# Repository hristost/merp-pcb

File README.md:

This is a PCB for a bluetooth split 12x5 ortholinear keyboard:
* Based on Adafruit's 32u4 
[Feather](https://github.com/adafruit/Adafruit-Feather-32u4-Bluefruit-LE-PCB)
beard. 
* Wireless (BLE) and wired (USB-C) mode.
* LED backlight.
* There are two 6x2 halves with identical PCBs. The _master_ half runs the QMK
firmware, and handles USB, BLE and battery charging. The _slave_ half is
responsible for only reporting its state to _master_ over I2C.
* Extra TRRS jack on the _slave_ half, making it possible to chain other I2C 
peripherals (think pedals).
* The board is flashed with the QMK firmware -- see my
[fork](https://github.com/hristost/qmk_firmware/tree/hristost_merp/keyboards/merp)
.

## Bluetooth
The PCB uses the Raytac MDBT-40 module for bluetooth. QMK has built-in support
for that module when flashed with Adafruit's 
[SPIFriend](https://github.com/adafruit/Adafruit_BluefruitLE_Firmware) firmware.

Since the Bluetooth module connects to the SPI bus, remember to flash the CPU
_before_ the Bluetooth module. Otherwise, the SPI bus will be taken and ICSP 
won't work.

## LED backlight
This keyboard has LED backlight, however:
* The drivers I used (TLC59711) draw quite some current on stand-by that makes
them unsuitable for battery-powered devices. I chose them because I already had
some left over from a previous project.
* Since the keyboard is "borderless", some switches have been rotated so that
components can fit between them. As a result, the backlight is uneven and would
not be suitable for actual backlit keys.
* The two halves operate backlight independently as of now, so any advanced
animation would have to utilise the I2C bus.
    
## Known issues:
I designed this keyboard just for fun and as such it has some shortcomings:
* The BLE module is somewhat hard to come by -- Mouser has it but it was out of
stock the few times I checked. Moreover, the Adafruit firmware for it
is closed source and you can only download binary images.
* Power management could be a lot better. Moreover, the keyboeard does not 
really have a stand-by state, instead, there is a switch that simply cuts all
power from the battery.
* The BLE module has enough processing
power to handle everything the CPU does now, but can't quite run QMK as of now.
(Another reason for sticking with _32u4_ is that it can easily be programmed
over USB)

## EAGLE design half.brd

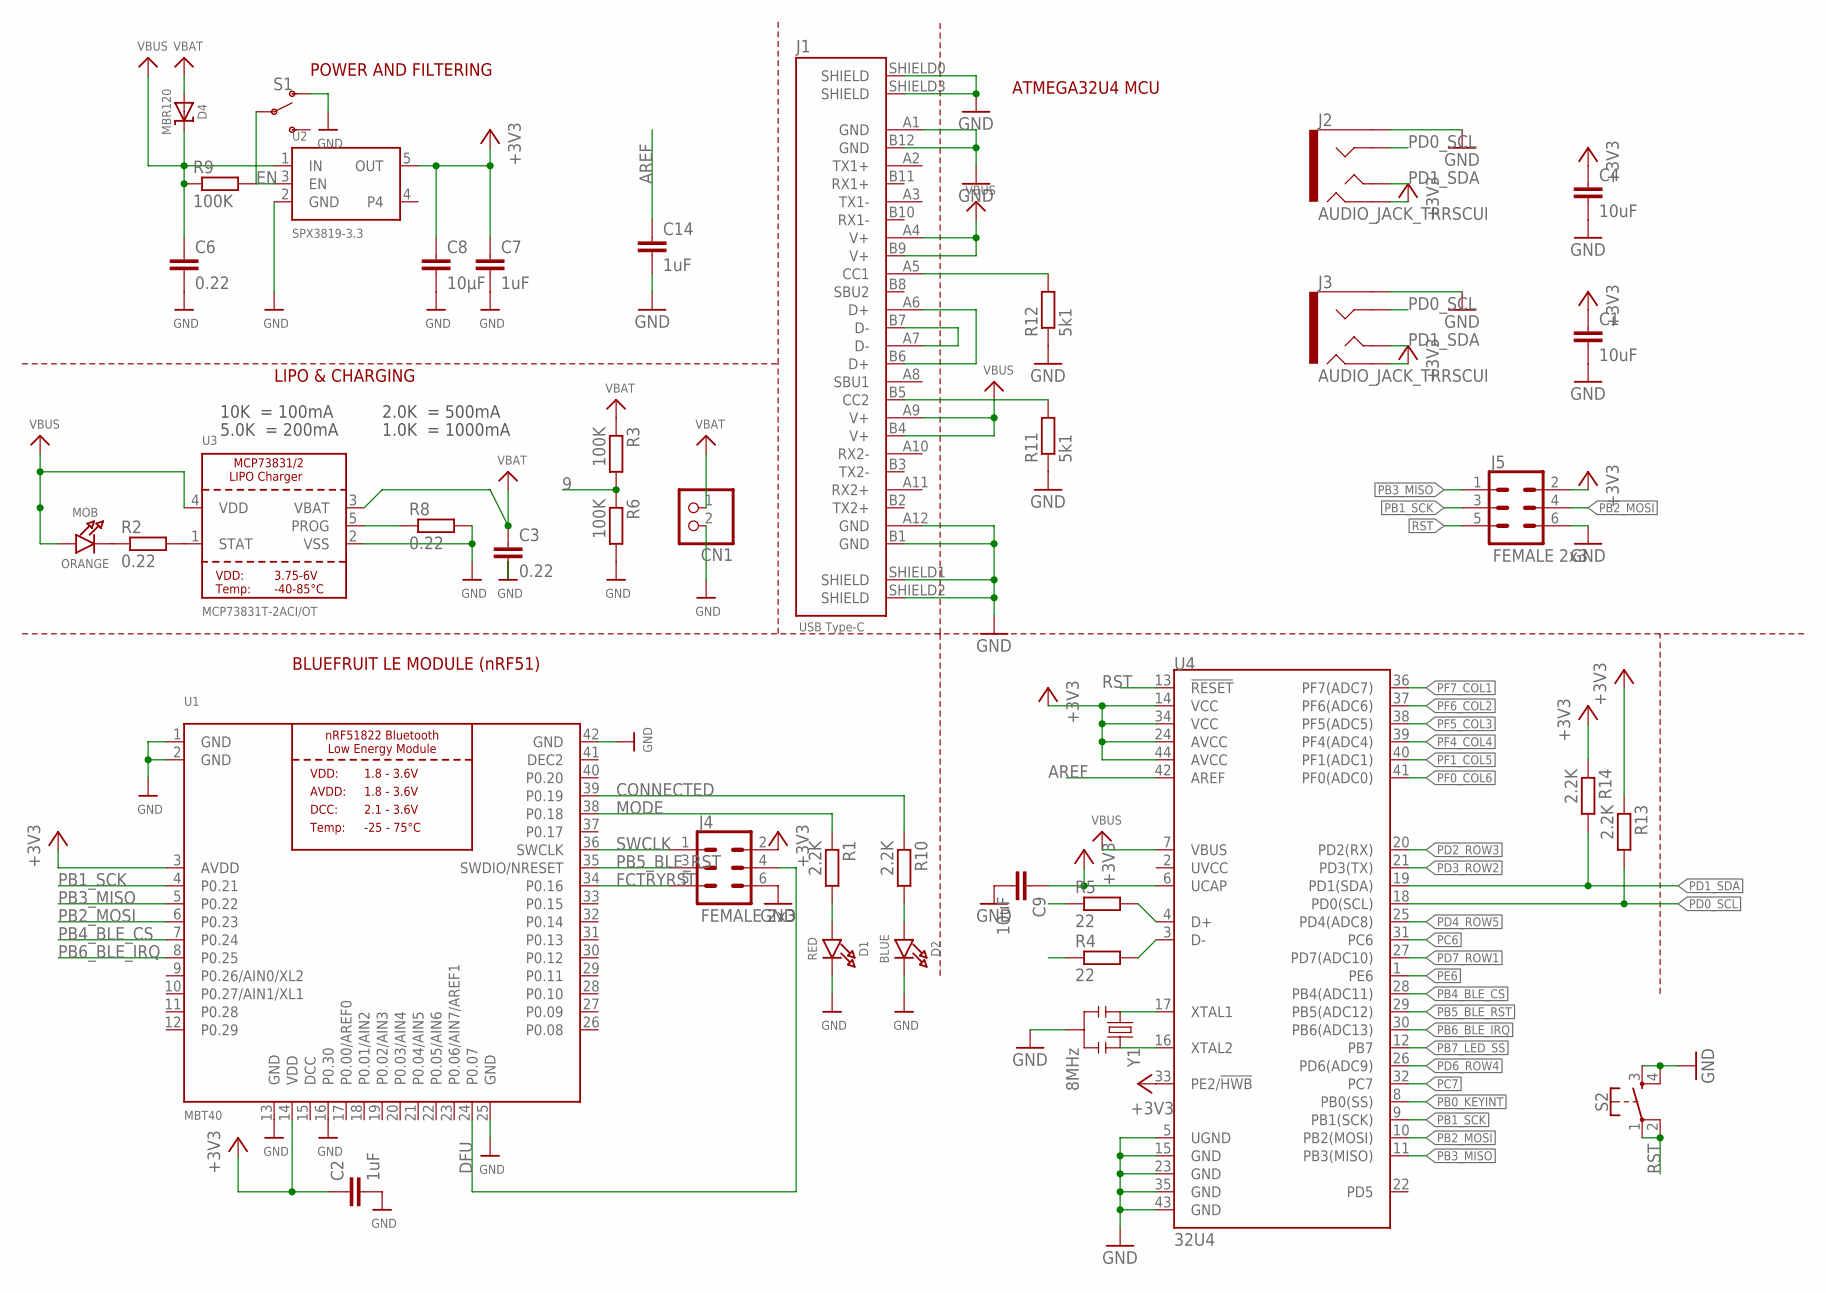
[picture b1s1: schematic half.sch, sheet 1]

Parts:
C1, C4, C9: 10uF; C0805
C2, C7, C14: 1uF; C0805
C3, C6: 0.22; C0805
C8: 10µF; C0805
CN1: JST_2PIN-SMT-RA; JST-PH-2-SMT-RA
D1: RED; CHIPLED_0805_NOOUTLINE
D2: BLUE; CHIPLED_0805_NOOUTLINE
D4: MBR120; SOD-123
J1: DX07S024JJ2_USB_TYPE-C; DX07S0224JJ2_USB-C
J2, J3: AUDIO_JACK_TRRSCUI; AUDIO_JACK_3.5MM_TRRS_SMD_CUI
J4, J5: FEMALE 2x3; 2X3
MOB: ORANGE; CHIPLED_0805_NOOUTLINE
R1, R10, R13, R14: 2.2K; R0805
R2, R8: 0.22; R0805
R3, R6, R9: 100K; R0805
R4, R5: 22; R0805
R11, R12: 5k1; R0805
S1: SWITCH-SPDT-SMD-RIGHT-ANGLE; SWITCH_SPST_SMD_A
S2: MOMENTARY-SWITCH-SPST-2-SMD-5.2MM; TACTILE_SWITCH_SMD_5.2MM
U1: MBT40; BLE_MODULE_RAYTAC_MDBT40
U2: SPX3819-3.3; SOT23-5
U3: MCP73831T-2ACI/OT; SOT23-5
U4: 32U4; TQFP44
Y1: 8MHz; RESONATOR-SMD

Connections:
9: R3.2, R6.1
+3V3: C1.1, C2.1, C4.1, C7.1, C8.1, C9.1, J2.RING2, J3.RING2, J4.2, J5.2, R13.1, R14.1, U1.3 (AVDD), U1.14 (VDD), U2.5 (OUT), U4.6 (UCAP), U4.14 (VCC), U4.24 (AVCC), U4.33 (PE2/!HWB), U4.34 (VCC), U4.44 (AVCC); also elsewhere on the board
AREF: C14.1, U4.42 (AREF)
CONNECTED: R10.1, U1.39 (P0.19)
D++: J1.A6 (D+), J1.B6 (D+), R5.1
D--: J1.A7 (D-), J1.B7 (D-), R4.1
DCC: U1.15 (DCC)
DEC2: U1.41 (DEC2)
DFU: J4.4, U1.24 (P0.07)
EN: R9.2, S1.2, U2.3 (EN)
FCTRYRST: J4.5, U1.34 (P0.16)
GND: C1.2, C2.2, C3.2, C4.2, C6.2, C7.2, C8.2, C9.2, C14.2, CN1.2 (1), D1.C, D2.C, J1.A1 (GND), J1.A12 (GND), J1.B1 (GND), J1.B12 (GND), J1.SHIELD0 (SHIELD), J1.SHIELD1 (SHIELD), J1.SHIELD2 (SHIELD), J1.SHIELD3 (SHIELD), J2.EARTH, J3.EARTH, J4.6, J5.6, R6.2, R8.2, R11.1, R12.1, S1.1 (O), S2.3, S2.4, U1.1 (GND), U1.2 (GND), U1.13 (GND), U1.16 (P0.30), U1.25 (GND), U1.42 (GND), U2.2 (GND), U3.2 (VSS), U4.5 (UGND), U4.15 (GND), U4.23 (GND), U4.35 (GND), U4.43 (GND), Y1.2; also elsewhere on the board
MODE: R1.1, U1.38 (P0.18)
unnamed: MOB.C, R2.1
unnamed: R2.2, U3.1 (STAT)
unnamed: R8.1, U3.5 (PROG)
unnamed: D1.A, R1.2
unnamed: D2.A, R10.2
unnamed: U4.17 (XTAL1), Y1.1
unnamed: U4.16 (XTAL2), Y1.3
unnamed: R5.2, U4.4 (D+)
unnamed: R4.2, U4.3 (D-)
unnamed: J1.A5 (CC1), R12.2
unnamed: J1.B5 (CC2), R11.2
PB0_KEYINT: U4.8 (PB0(SS)); also elsewhere on the board
PB1_SCK: J5.3, U1.4 (P0.21), U4.9 (PB1(SCK)); also elsewhere on the board
PB2_MOSI: J5.4, U1.6 (P0.23), U4.10 (PB2(MOSI)); also elsewhere on the board
PB3_MISO: J5.1, U1.5 (P0.22), U4.11 (PB3(MISO))
PB4_BLE_CS: U1.7 (P0.24), U4.28 (PB4(ADC11))
PB5_BLE_RST: J4.3, U1.35 (SWDIO/NRESET), U4.29 (PB5(ADC12))
PB6_BLE_IRQ: U1.8 (P0.25), U4.30 (PB6(ADC13))
PB7_LED_SS: U4.12 (PB7); also elsewhere on the board
PC6: U4.31 (PC6)
PC7: U4.32 (PC7)
PD0_SCL: J2.RING1, J3.RING1, R13.2, U4.18 (PD0(SCL))
PD1_SDA: J2.TIP, J3.TIP, R14.2, U4.19 (PD1(SDA))
PD2_ROW3: U4.20 (PD2(RX)); also elsewhere on the board
PD3_ROW2: U4.21 (PD3(TX)); also elsewhere on the board
PD4_ROW5: U4.25 (PD4(ADC8)); also elsewhere on the board
PD6_ROW4: U4.26 (PD6(ADC9)); also elsewhere on the board
PD7_ROW1: U4.27 (PD7(ADC10)); also elsewhere on the board
PE6: U4.1 (PE6)
PF0_COL6: U4.41 (PF0(ADC0)); also elsewhere on the board
PF1_COL5: U4.40 (PF1(ADC1)); also elsewhere on the board
PF4_COL4: U4.39 (PF4(ADC4)); also elsewhere on the board
PF5_COL3: U4.38 (PF5(ADC5)); also elsewhere on the board
PF6_COL2: U4.37 (PF6(ADC6)); also elsewhere on the board
PF7_COL1: U4.36 (PF7(ADC7)); also elsewhere on the board
RST: J5.5, S2.1, S2.2, U4.13 (!RESET)
SWCLK: J4.1, U1.36 (SWCLK)
VBAT: C3.1, CN1.1 (2), D4.A, R3.1, U3.3 (VBAT)
VBUS: C6.1, D4.C, J1.A4 (V+), J1.A9 (V+), J1.B4 (V+), J1.B9 (V+), MOB.A, R9.1, U2.1 (IN), U3.4 (VDD), U4.7 (VBUS)

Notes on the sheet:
POWER AND FILTERING
BLUEFRUIT LE MODULE (nRF51)
ATMEGA32U4 MCU
10K = 100mA
5.0K = 200mA
2.0K = 500mA
1.0K = 1000mA
LIPO & CHARGING

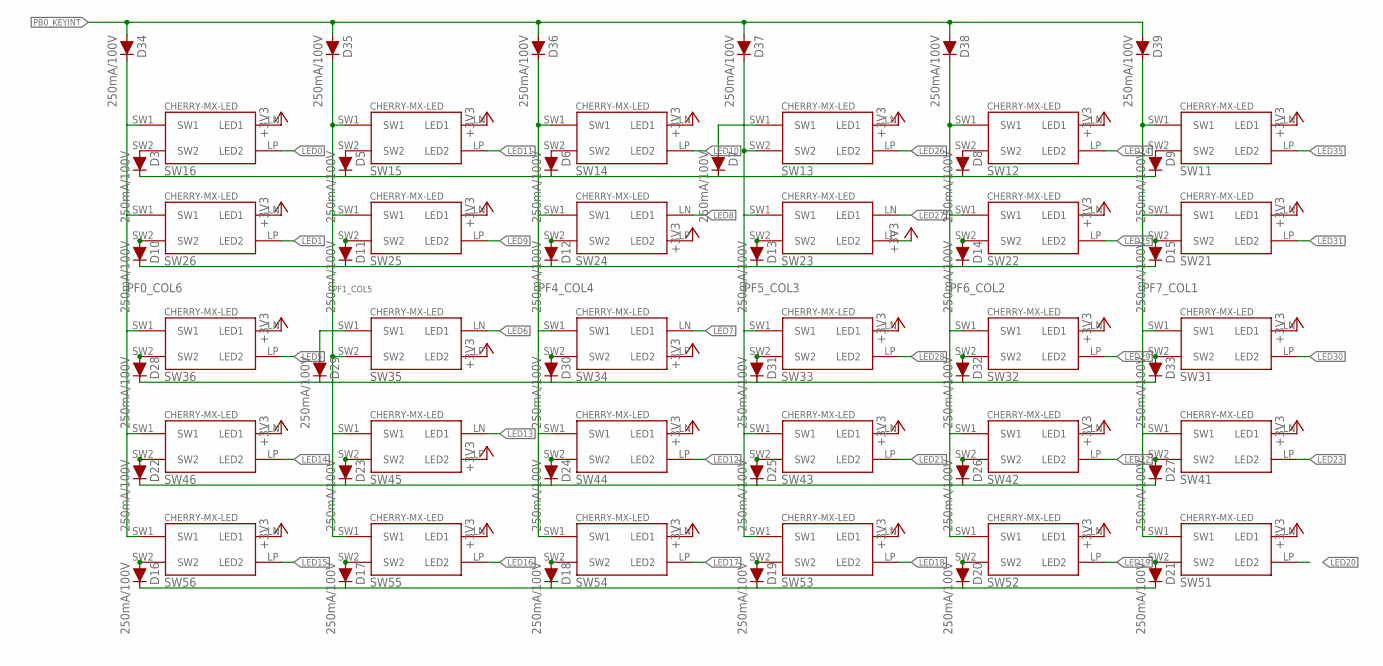
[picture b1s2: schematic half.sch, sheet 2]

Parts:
D3, D5, D6, D7, D8, D9, D10, D11, D12, D13, D14, D15, D16, D17, D18, D19, D20, D21, D22, D23, D24, D25, D26, D27, D28, D29, D30, D31, D32, D33, D34, D35, D36, D37, D38, D39: 250mA/100V; SOD-323
SW11, SW12, SW13, SW14, SW15, SW16, SW21, SW22, SW23, SW24, SW25, SW26, SW31, SW32, SW33, SW34, SW35, SW36, SW41, SW42, SW43, SW44, SW45, SW46, SW51, SW52, SW53, SW54, SW55, SW56: CHERRY-MX-LEDSMD; CHERRY-MX-PM-SMDLED

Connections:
+3V3: SW11.LN (LED1), SW12.LN (LED1), SW13.LN (LED1), SW14.LN (LED1), SW15.LN (LED1), SW16.LN (LED1), SW21.LN (LED1), SW22.LN (LED1), SW23.LP (LED2), SW24.LP (LED2), SW25.LN (LED1), SW26.LN (LED1), SW31.LN (LED1), SW32.LN (LED1), SW33.LN (LED1), SW34.LP (LED2), SW35.LP (LED2), SW36.LN (LED1), SW41.LN (LED1), SW42.LN (LED1), SW43.LN (LED1), SW44.LN (LED1), SW45.LP (LED2), SW46.LN (LED1), SW51.LN (LED1), SW52.LN (LED1), SW53.LN (LED1), SW54.LN (LED1), SW55.LN (LED1), SW56.LN (LED1); also elsewhere on the board
LED0: SW16.LP (LED2); also elsewhere on the board
LED1: SW26.LP (LED2); also elsewhere on the board
LED5: SW36.LP (LED2); also elsewhere on the board
LED6: SW35.LN (LED1); also elsewhere on the board
LED7: SW34.LN (LED1); also elsewhere on the board
LED8: SW24.LN (LED1); also elsewhere on the board
LED9: SW25.LP (LED2); also elsewhere on the board
LED10: SW14.LP (LED2); also elsewhere on the board
LED11: SW15.LP (LED2); also elsewhere on the board
LED12: SW44.LP (LED2); also elsewhere on the board
LED13: SW45.LN (LED1); also elsewhere on the board
LED14: SW46.LP (LED2); also elsewhere on the board
LED15: SW56.LP (LED2); also elsewhere on the board
LED16: SW55.LP (LED2); also elsewhere on the board
LED17: SW54.LP (LED2); also elsewhere on the board
LED18: SW53.LP (LED2); also elsewhere on the board
LED19: SW52.LP (LED2); also elsewhere on the board
LED20: SW51.LP (LED2); also elsewhere on the board
LED21: SW43.LP (LED2); also elsewhere on the board
LED22: SW42.LP (LED2); also elsewhere on the board
LED23: SW41.LP (LED2); also elsewhere on the board
LED24: SW12.LP (LED2); also elsewhere on the board
LED25: SW22.LP (LED2); also elsewhere on the board
LED26: SW13.LP (LED2); also elsewhere on the board
LED27: SW23.LN (LED1); also elsewhere on the board
LED28: SW33.LP (LED2); also elsewhere on the board
LED29: SW32.LP (LED2); also elsewhere on the board
LED30: SW31.LP (LED2); also elsewhere on the board
LED31: SW21.LP (LED2); also elsewhere on the board
LED35: SW11.LP (LED2); also elsewhere on the board
unnamed: D29.A, SW35.SW1
unnamed: D3.A, SW16.SW2
unnamed: D5.A, SW15.SW2
unnamed: D6.A, SW14.SW2
unnamed: D7.A, SW13.SW1
unnamed: D8.A, SW12.SW2
unnamed: D9.A, SW11.SW2
unnamed: D10.A, SW26.SW2
unnamed: D11.A, SW25.SW2
unnamed: D12.A, SW24.SW2
unnamed: D13.A, SW23.SW2
unnamed: D14.A, SW22.SW2
unnamed: D15.A, SW21.SW2
unnamed: D16.A, SW56.SW2
unnamed: D17.A, SW55.SW2
unnamed: D18.A, SW54.SW2
unnamed: D19.A, SW53.SW2
unnamed: D20.A, SW52.SW2
unnamed: D21.A, SW51.SW2
unnamed: D22.A, SW46.SW2
unnamed: D23.A, SW45.SW2
unnamed: D24.A, SW44.SW2
unnamed: D25.A, SW43.SW2
unnamed: D26.A, SW42.SW2
unnamed: D27.A, SW41.SW2
unnamed: D28.A, SW36.SW2
unnamed: D30.A, SW34.SW2
unnamed: D31.A, SW33.SW2
unnamed: D32.A, SW32.SW2
unnamed: D33.A, SW31.SW2
PB0_KEYINT: D34.A, D35.A, D36.A, D37.A, D38.A, D39.A; also elsewhere on the board
PD2_ROW3: D28.C, D29.C, D30.C, D31.C, D32.C, D33.C; also elsewhere on the board
PD3_ROW2: D10.C, D11.C, D12.C, D13.C, D14.C, D15.C; also elsewhere on the board
PD4_ROW5: D16.C, D17.C, D18.C, D19.C, D20.C, D21.C; also elsewhere on the board
PD6_ROW4: D22.C, D23.C, D24.C, D25.C, D26.C, D27.C; also elsewhere on the board
PD7_ROW1: D3.C, D5.C, D6.C, D7.C, D8.C, D9.C; also elsewhere on the board
PF0_COL6: D34.C, SW16.SW1, SW26.SW1, SW36.SW1, SW46.SW1, SW56.SW1; also elsewhere on the board
PF1_COL5: D35.C, SW15.SW1, SW25.SW1, SW35.SW2, SW45.SW1, SW55.SW1; also elsewhere on the board
PF4_COL4: D36.C, SW14.SW1, SW24.SW1, SW34.SW1, SW44.SW1, SW54.SW1; also elsewhere on the board
PF5_COL3: D37.C, SW13.SW2, SW23.SW1, SW33.SW1, SW43.SW1, SW53.SW1; also elsewhere on the board
PF6_COL2: D38.C, SW12.SW1, SW22.SW1, SW32.SW1, SW42.SW1, SW52.SW1; also elsewhere on the board
PF7_COL1: D39.C, SW11.SW1, SW21.SW1, SW31.SW1, SW41.SW1, SW51.SW1; also elsewhere on the board

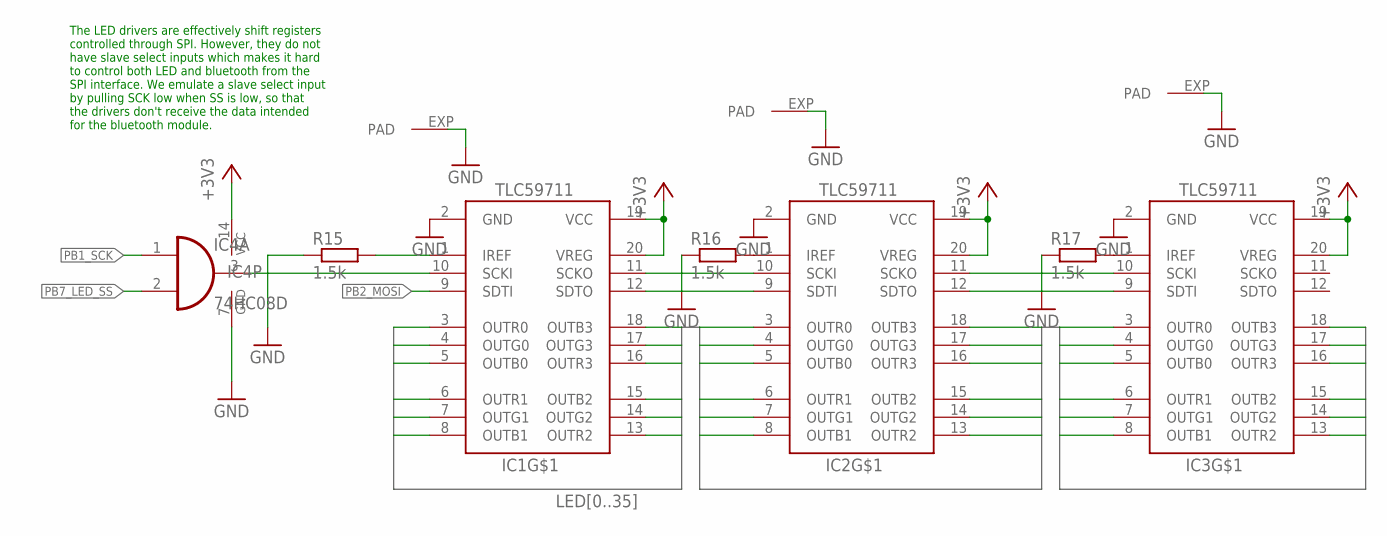
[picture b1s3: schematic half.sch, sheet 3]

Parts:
IC1, IC2, IC3: TLC59711; HTSSOP20DAP
IC4: 74HC08D; SO14
R15, R16, R17: 1.5k; R0805

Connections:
+3V3: IC1.19 (VCC), IC1.20 (VREG), IC2.19 (VCC), IC2.20 (VREG), IC3.19 (VCC), IC3.20 (VREG), IC4.14 (VCC); also elsewhere on the board
GND: IC1.2 (GND), IC1.EXP (PAD), IC2.2 (GND), IC2.EXP (PAD), IC3.2 (GND), IC3.EXP (PAD), IC4.7 (GND), R15.1, R16.1, R17.1; also elsewhere on the board
LED0: IC1.3 (OUTR0); also elsewhere on the board
LED1: IC1.4 (OUTG0); also elsewhere on the board
LED2: IC1.5 (OUTB0)
LED3: IC1.6 (OUTR1)
LED4: IC1.7 (OUTG1)
LED5: IC1.8 (OUTB1); also elsewhere on the board
LED6: IC1.13 (OUTR2); also elsewhere on the board
LED7: IC1.14 (OUTG2); also elsewhere on the board
LED8: IC1.15 (OUTB2); also elsewhere on the board
LED9: IC1.16 (OUTR3); also elsewhere on the board
LED10: IC1.17 (OUTG3); also elsewhere on the board
LED11: IC1.18 (OUTB3); also elsewhere on the board
LED12: IC2.3 (OUTR0); also elsewhere on the board
LED13: IC2.4 (OUTG0); also elsewhere on the board
LED14: IC2.5 (OUTB0); also elsewhere on the board
LED15: IC2.6 (OUTR1); also elsewhere on the board
LED16: IC2.7 (OUTG1); also elsewhere on the board
LED17: IC2.8 (OUTB1); also elsewhere on the board
LED18: IC2.13 (OUTR2); also elsewhere on the board
LED19: IC2.14 (OUTG2); also elsewhere on the board
LED20: IC2.15 (OUTB2); also elsewhere on the board
LED21: IC2.16 (OUTR3); also elsewhere on the board
LED22: IC2.17 (OUTG3); also elsewhere on the board
LED23: IC2.18 (OUTB3); also elsewhere on the board
LED24: IC3.3 (OUTR0); also elsewhere on the board
LED25: IC3.4 (OUTG0); also elsewhere on the board
LED26: IC3.5 (OUTB0); also elsewhere on the board
LED27: IC3.6 (OUTR1); also elsewhere on the board
LED28: IC3.7 (OUTG1); also elsewhere on the board
LED29: IC3.8 (OUTB1); also elsewhere on the board
LED30: IC3.13 (OUTR2); also elsewhere on the board
LED31: IC3.14 (OUTG2); also elsewhere on the board
LED32: IC3.15 (OUTB2)
LED33: IC3.16 (OUTR3)
LED34: IC3.17 (OUTG3)
LED35: IC3.18 (OUTB3); also elsewhere on the board
LEDDAT2: IC1.12 (SDTO), IC2.9 (SDTI)
LEDDAT3: IC2.12 (SDTO), IC3.9 (SDTI)
LEDSCK1: IC1.10 (SCKI), IC4.3 (O)
LEDSCK2: IC1.11 (SCKO), IC2.10 (SCKI)
LEDSCK3: IC2.11 (SCKO), IC3.10 (SCKI)
unnamed: IC1.1 (IREF), R15.2
unnamed: IC3.1 (IREF), R17.2
unnamed: IC2.1 (IREF), R16.2
PB1_SCK: IC4.1 (I0); also elsewhere on the board
PB2_MOSI: IC1.9 (SDTI); also elsewhere on the board
PB7_LED_SS: IC4.2 (I1); also elsewhere on the board

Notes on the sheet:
The LED drivers are effectively shift registers controlled through SPI. However, they do not have slave select inputs which makes it hard to control both LED and bluetooth from the SPI interface. We emulate a slave select input by pulling SCK low when SS is low, so that the drivers don't receive th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

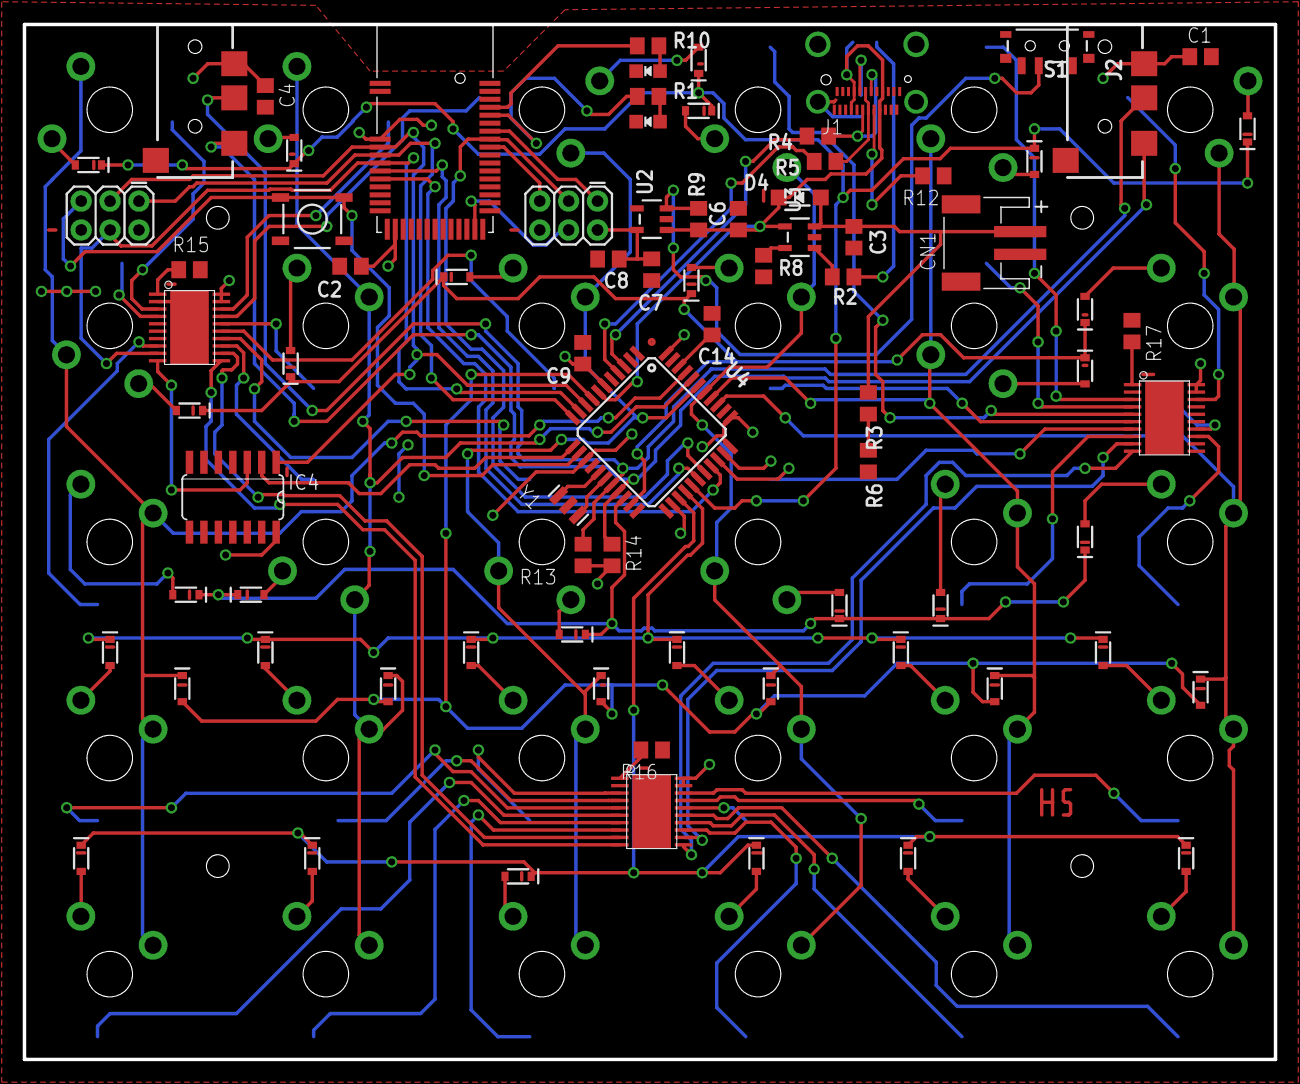
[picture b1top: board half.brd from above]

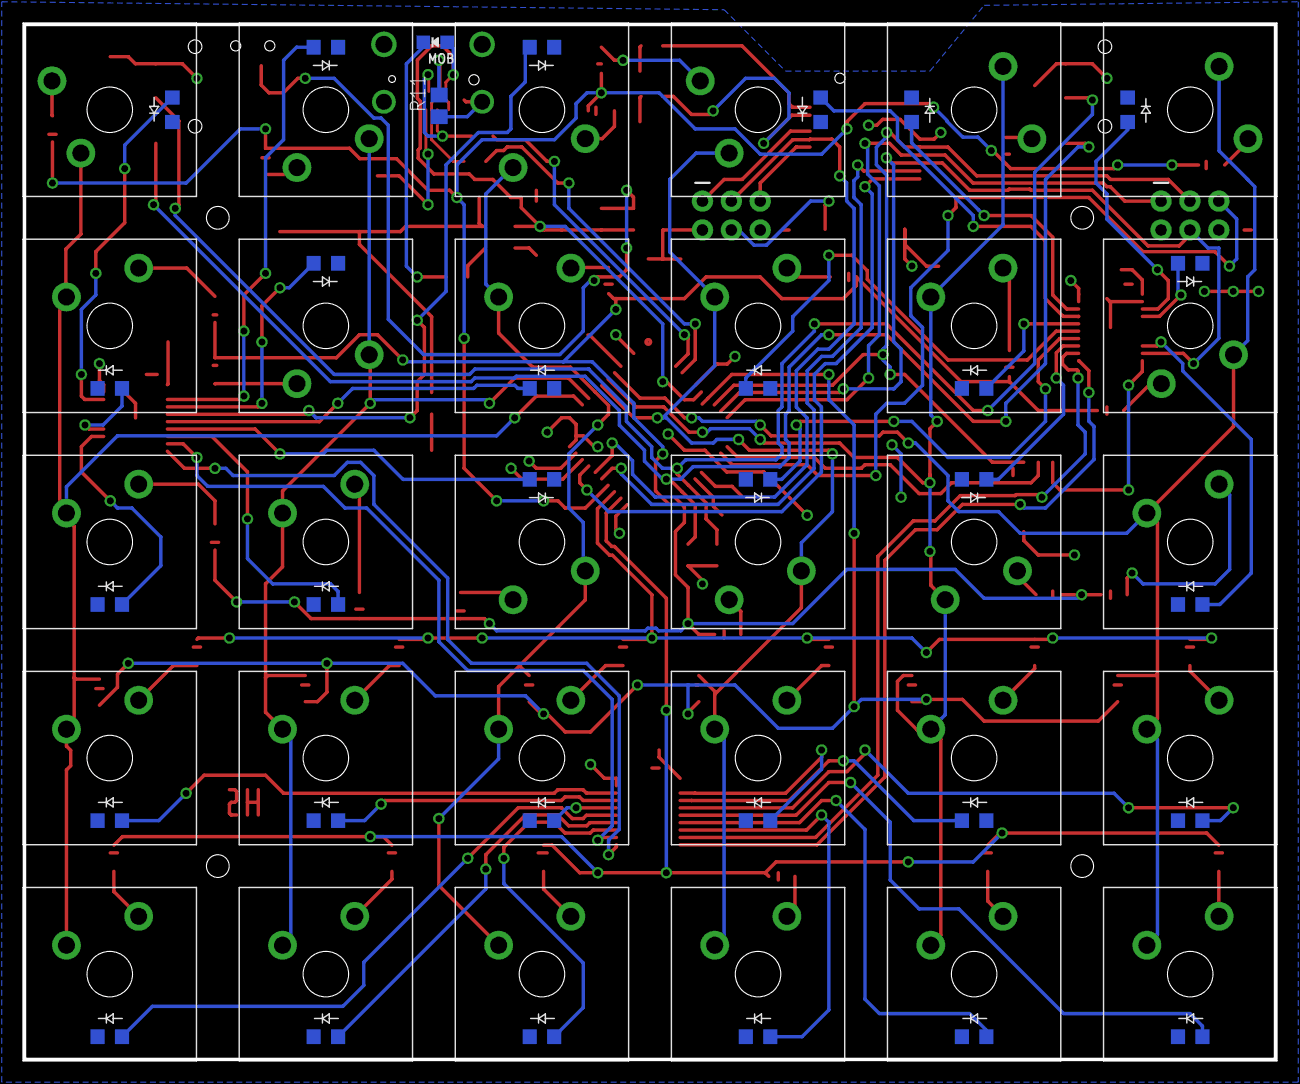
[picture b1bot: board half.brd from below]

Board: 2 copper layers, 110.0 x 91.0 mm, 112 parts (32 on the bottom side), 115 nets.

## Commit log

2018-10-12 Inital commit
2018-10-12 Disconnect UVCC on 32u4 to reflect a greenwire fix on PCB
2018-10-12 Fix readme markdown

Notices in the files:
parts and their libraries:
microbuilder: This work is placed in the public domain, and may be freely used for commercial and non-commercial work with the following conditions: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
SparkFun: Licensing: CC v3.0 Share-Alike You are welcome to use this library for commercial purposes.
